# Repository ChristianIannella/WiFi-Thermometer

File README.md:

# WiFi-Thermometer

Italiano/English

WiFi Thermometer è un dispositivo IoT pronto all'uso ma con la possibilità di cambiare firmware in modo semplice tramite connettore dedicato.

A bordo è presente un AC/DC (RAC02-3.3SGB), un ESP8266 (mod. ESP12) e un sensore di temperatura/umidità (HTU21D).
Ti basterà alimentare la scheda tramite il connettore a morsetti direttamente alla tensione di rete oppure tramite pin 1 (GND) e pin 6 (3.3v) del
connettore per la programmazione.
ATTENZIONE! NON ALIMENTARE LA SCHEDA CON I DUE METODI CONTEMPORANEAMENTE.
Per aggiornare o cambiare il firmware avrai bisogno del programmatore o un convertitore USB/UART come il CH340G ATTENZIONE! IL CONVERTITORE DEVE LAVORARE A 3.3V

PINOUT

1: GND

2: GPIO2

3: GPIO0

4: RX

5: TX

6: VCC 3.3v

COME FUNZIONA

Al momento dell accensione se non è stato gia configurato il dispositivo metterà a disposizione un access point (SSID: WiFi Thermometer, Password:12345678)
tramite il quale sara possibile inserire SSID e Password della propria rete lan.

You can find WiFi Thermometer on Tindie

(This page is work in progress!)

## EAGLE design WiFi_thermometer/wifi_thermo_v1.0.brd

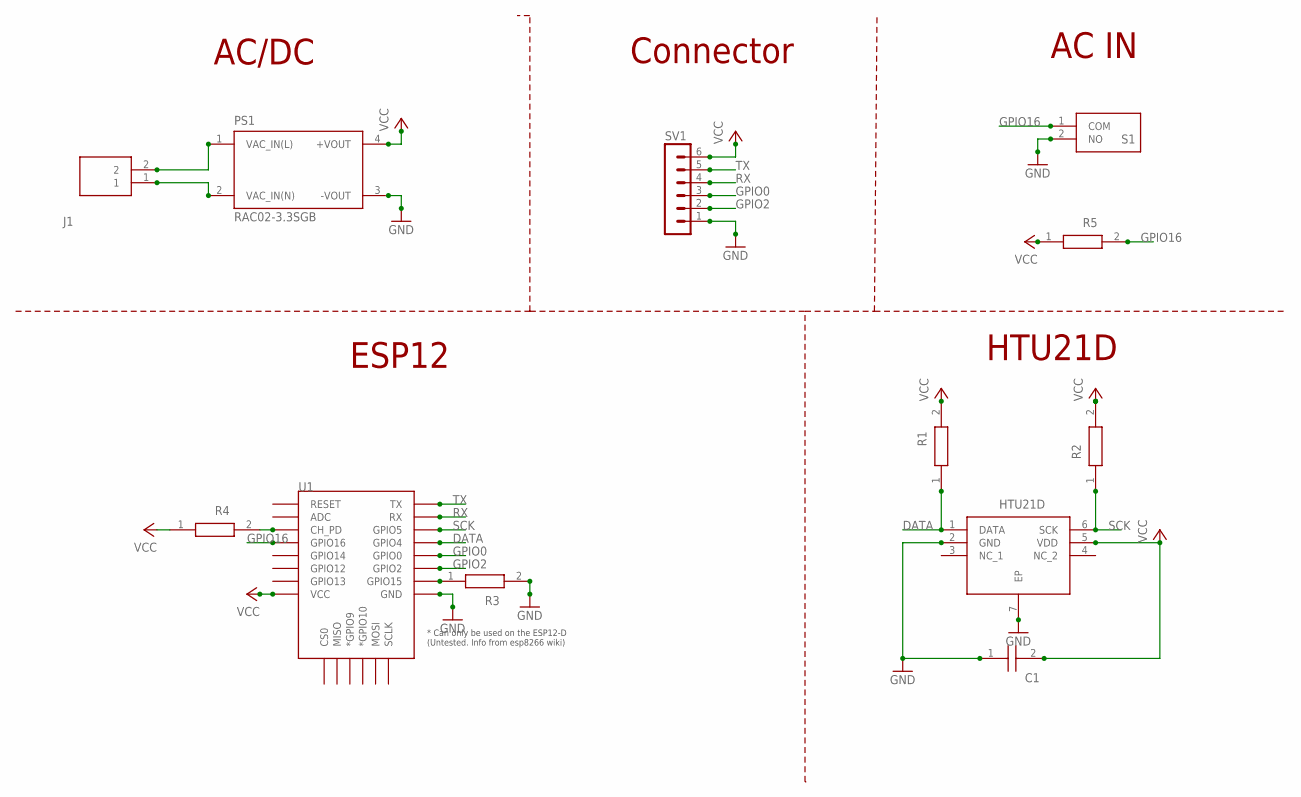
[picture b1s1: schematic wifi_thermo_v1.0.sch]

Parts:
C1: C1206C104J3GEC7210; CAPC3216X110N
HM1: HTU21D; SON100P300X300X100-7N
J1: TB006-508-02BE; TB00650802BE
PS1: RAC02-3.3SGB; CONV_RAC02-3.3SGB
R1, R2, R3, R4, R5: RT1206FRD0710KL; RESC3116X65N
S1: PTS636_SP50_SMTR_LFS; PTS636SP50SMTRLFS
SV1: MA06-1
U1: ESP12ESMD; ESP12E-SMD

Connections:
DATA: HM1.1 (DATA), R1.1, U1.GPIO4
GND: C1.1, HM1.2 (GND), HM1.7 (EP), PS1.3 (-VOUT), R3.2, S1.2 (NO), SV1.1, U1.GND
GPIO0: SV1.3, U1.GPIO0
GPIO2: SV1.2, U1.GPIO2
GPIO16: R5.2, S1.1 (COM), U1.GPIO16
unnamed: J1.2, PS1.1 (VAC_IN(L))
unnamed: J1.1, PS1.2 (VAC_IN(N))
unnamed: R3.1, U1.GPIO15
unnamed: R4.2, U1.CH_PD
RX: SV1.4, U1.RXD0 (RX)
SCK: HM1.6 (SCK), R2.1, U1.GPIO5
TX: SV1.5, U1.TXD0 (TX)
VCC: C1.2, HM1.5 (VDD), PS1.4 (+VOUT), R1.2, R2.2, R4.1, R5.1, SV1.6, U1.VCC

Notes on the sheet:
AC/DC
Connector
AC IN
HTU21D
ESP12

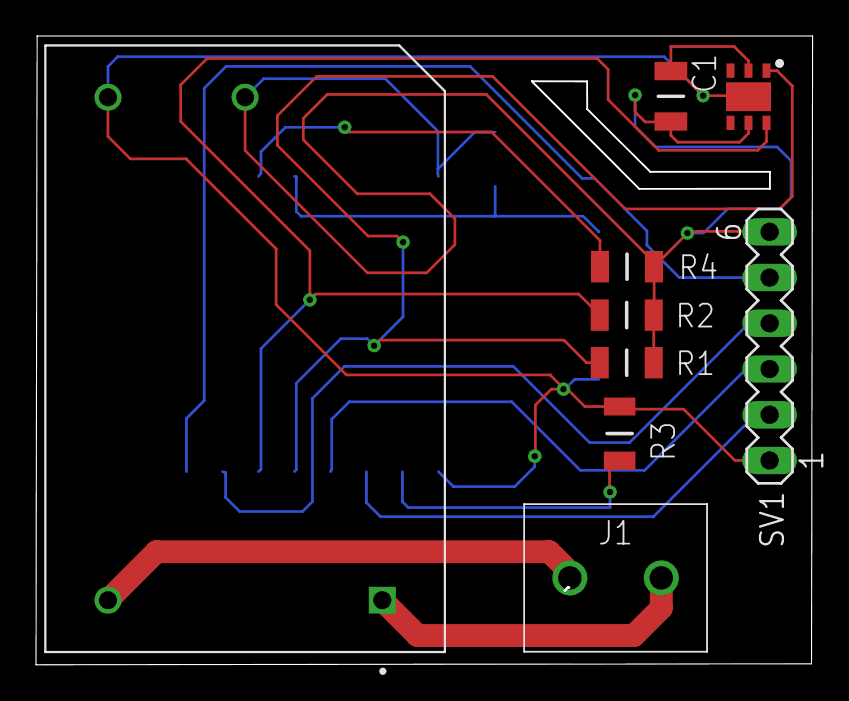
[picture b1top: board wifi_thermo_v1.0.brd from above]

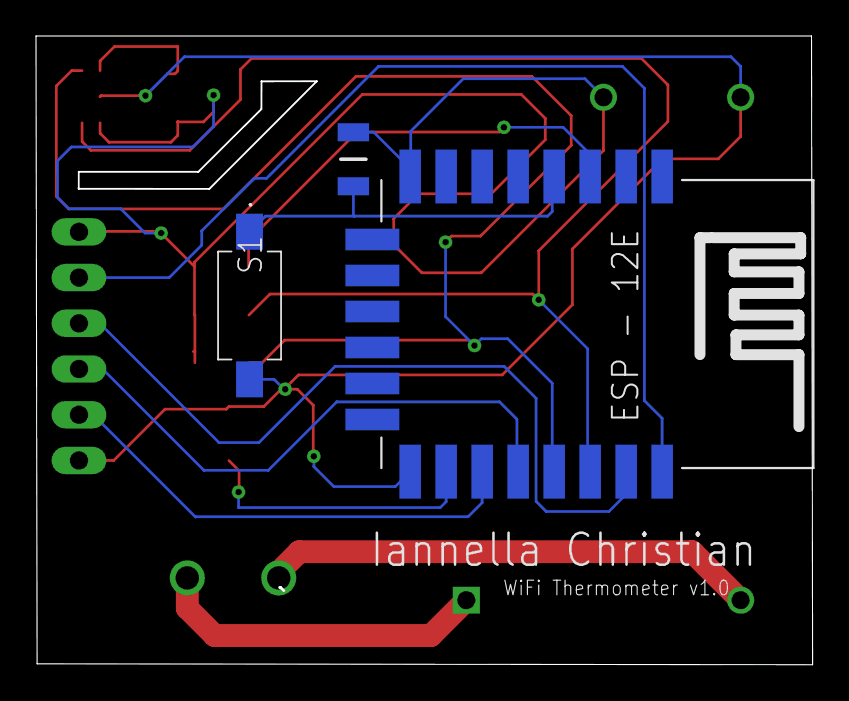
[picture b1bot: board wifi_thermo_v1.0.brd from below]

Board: 2 copper layers, 43.0 x 34.8 mm, 12 parts (3 on the bottom side), 13 nets.
